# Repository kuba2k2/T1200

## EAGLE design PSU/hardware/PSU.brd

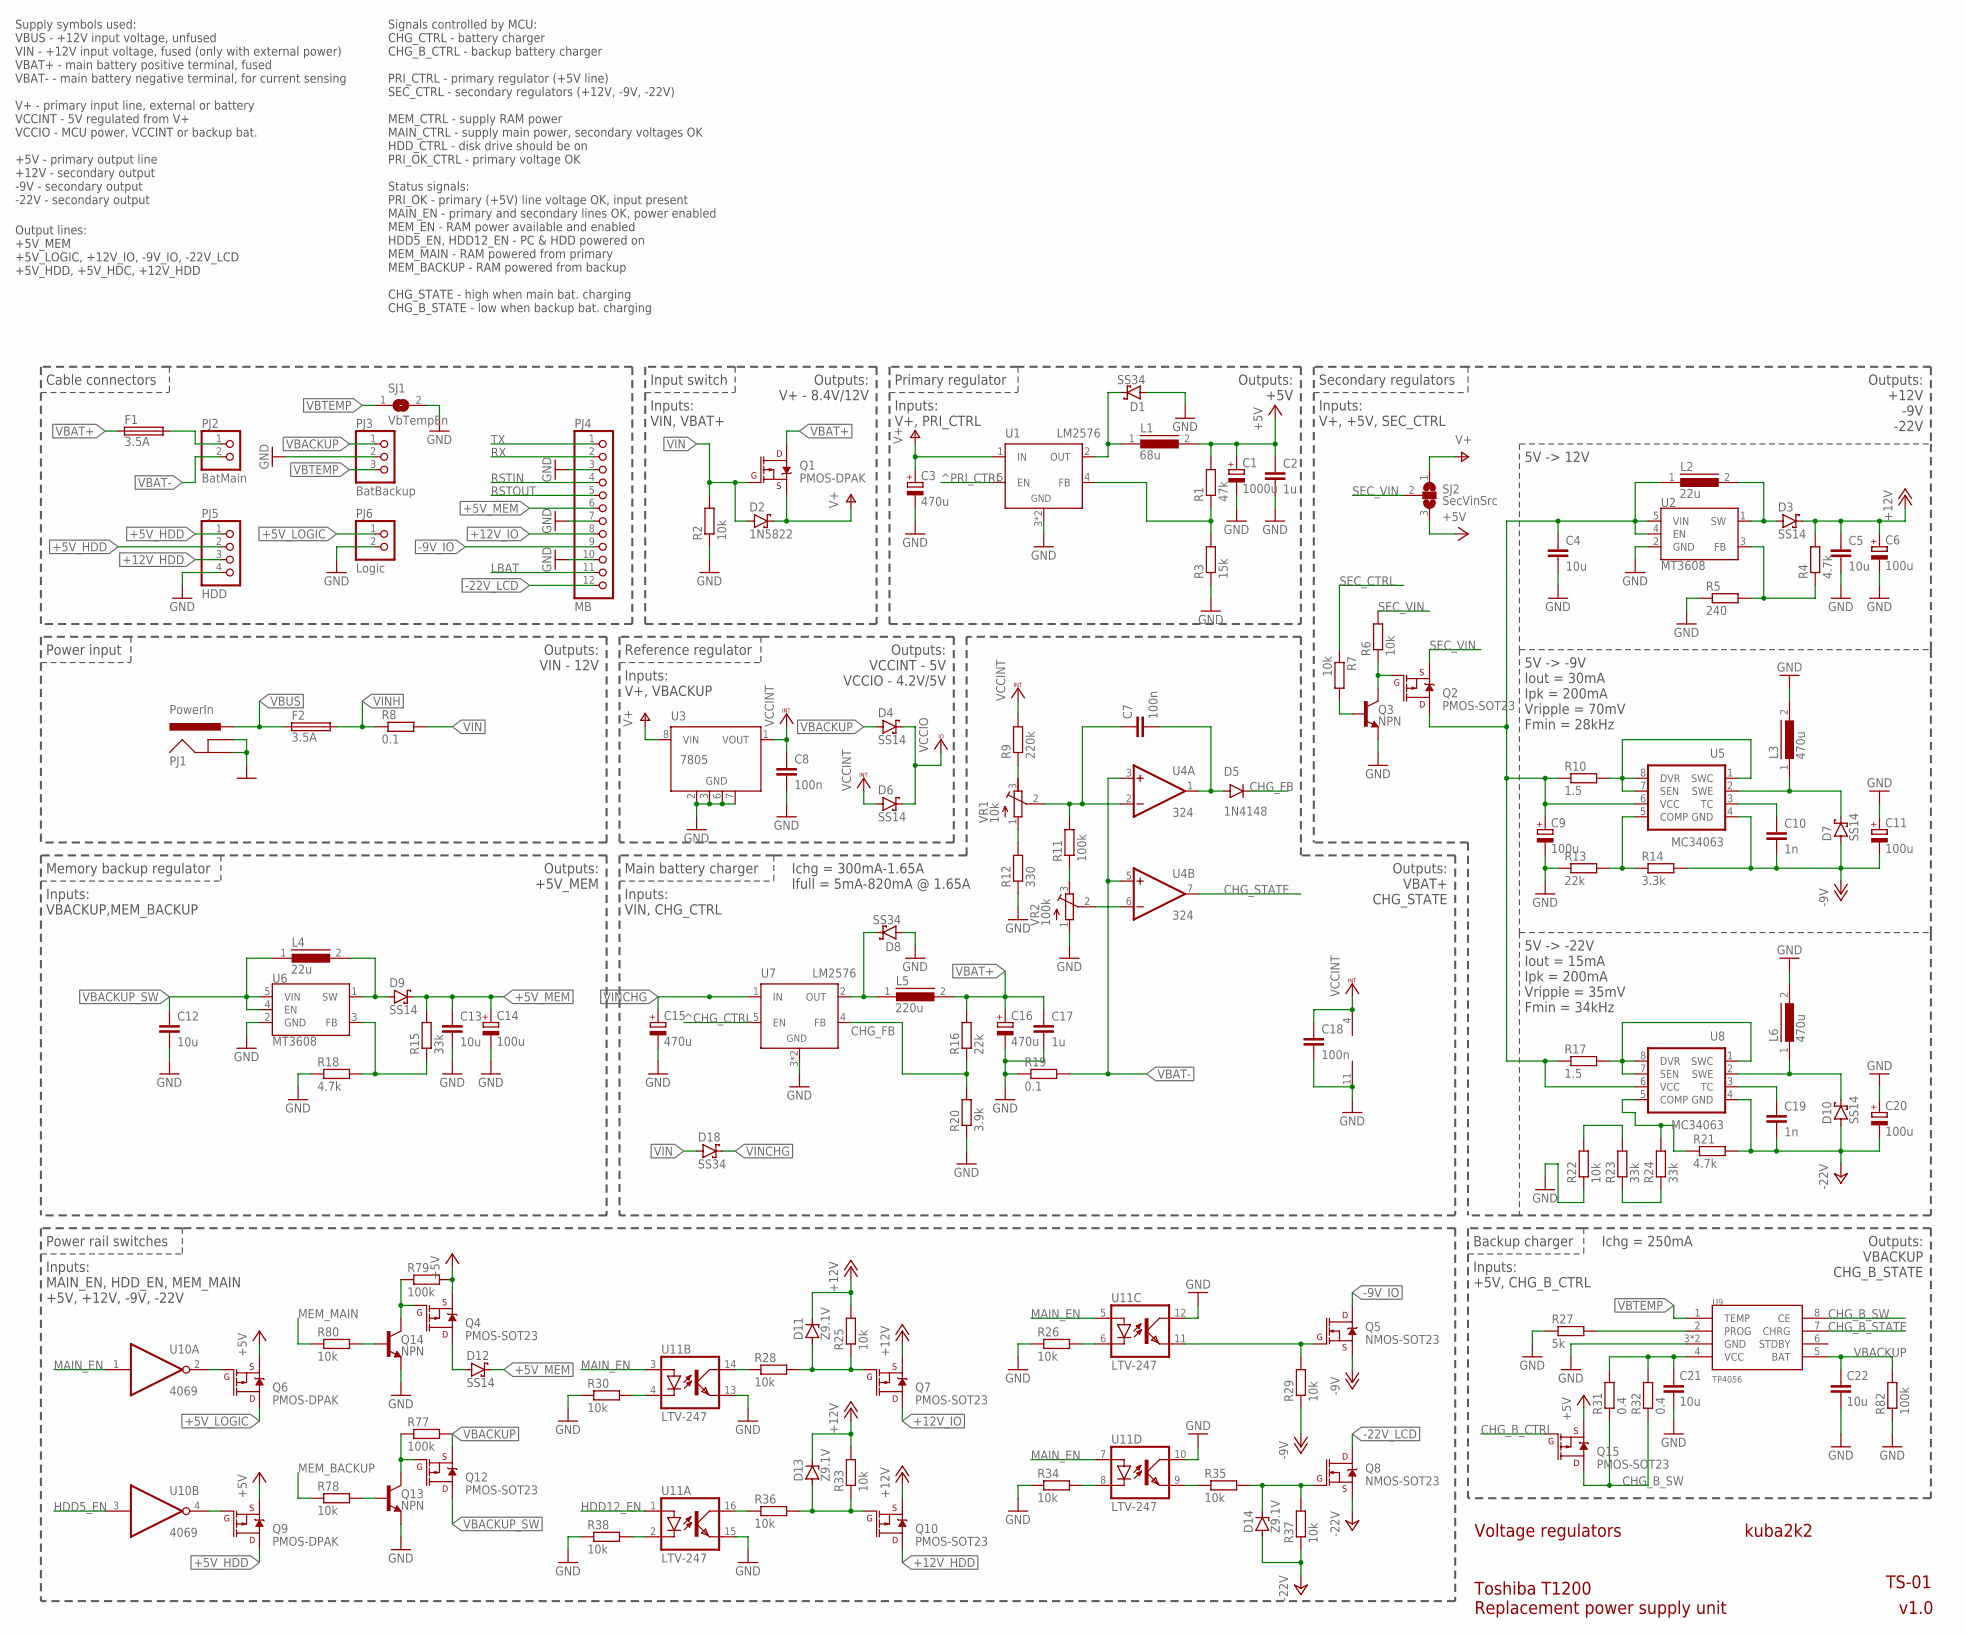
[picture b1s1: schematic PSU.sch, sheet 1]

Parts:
C1: 1000u; E5-10,5
C2, C17: 1u; C050-024X044
C3, C15, C16: 470u; E3,5-8
C4, C5, C12, C13, C21, C22: 10u; C1206
C6, C9, C11, C14, C20: 100u; E3,5-8
C7, C8, C18: 100n; C0805
C10, C19: 1n; C0805
D1, D8, D18: SS34; SMC
D2: 1N5822; F126Z12
D3, D4, D6, D7, D9, D10, D12: SS14; DO-214AC
D5: 1N4148; DO35-7
D11, D13, D14: Z9.1V; DO34Z7
F1, F2: 3.5A; 2512
L1: 68u; SFT1030
L2, L4: 22u; DR127
L3, L6: 470u; COIL0608
L5: 220u; SFT1030
PJ1: PowerIn; POWER_JACK_PTH
PJ2: BatMain; JST-PH2-4.00
PJ3: BatBackup; JST-PH3
PJ4: MB; JST-PH12
PJ5: HDD; JST-PH4-2.54
PJ6: Logic; JST-PH2-2.54
Q1, Q6, Q9: PMOS-DPAK; TO-252/DPAK
Q2, Q4, Q7, Q10, Q12, Q15: PMOS-SOT23; SOT23-3
Q3, Q13, Q14: NPN; SOT23-3
Q5, Q8: NMOS-SOT23; SOT23-3
R1: 47k; R0805
R2, R6, R7, R22, R25, R26, R28, R29, R30, R33, R34, R35, R36, R37, R38, R78, R80: 10k; R0805
R3: 15k; R0805
R4, R18, R21: 4.7k; R0805
R5: 240; R0805
R8, R19: 0.1; 0411/15
R9: 220k; R0805
R10, R17: 1.5; 0207/10
R11, R77, R79, R82: 100k; R0805
R12: 330; R0805
R13, R16: 22k; R0805
R14: 3.3k; R0805
R15, R23, R24: 33k; R0805
R20: 3.9k; R0805
R27: 5k; R0805
R31: 0.4; 0207/10
R32: 0.4; R1206
SJ1: VbTempEn; SJ
SJ2: SecVinSrc; SJ_2
U1, U7: LM2576; TO220-52-VIAHOLE
U2, U6: MT3608; SOT23-6
U3: 7805; SO08
U4: 324; SO14
U5, U8: MC34063; SO08
U9: TP4056; SO08-PAD
U10: 4069; SO14
U11: LTV-247; SO16-GULLWING
VR1: 10k; RTRIM3296W
VR2: 100k; RTRIM3296W

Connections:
+5V: C1.+, C2.1, L1.2, Q4.2 (S), Q6.3 (S), Q9.3 (S), Q15.2 (S), R1.2, R79.2, SJ2.3; also elsewhere on the board
+5VHDD_G: Q9.1 (G), U10.4 (O)
+5VLOG_G: Q6.1 (G), U10.2 (O)
+5VMEM_B: Q14.1 (B), R80.2
+5VMEM_D: D12.A, Q4.3 (D)
+5VMEM_G: Q4.1 (G), Q14.3 (C), R79.1
+5V_HDD: PJ5.1, PJ5.2, Q9.2 (D)
+5V_LOGIC: PJ6.1, Q6.2 (D)
+5V_MEM: C13.1, C14.+, D9.C, D12.C, PJ4.6, R15.2; also elsewhere on the board
+12V: C5.1, C6.+, D3.C, D11.C, D13.C, Q7.2 (S), Q10.2 (S), R4.2, R25.2, R33.2; also elsewhere on the board
+12VHDD_C: R36.1, U11.16 (COL)
+12VHDD_G: D13.A, Q10.1 (G), R33.1, R36.2
+12VHDD_N: R38.2, U11.2 (C)
+12VIO_C: R28.1, U11.14 (COL)
+12VIO_G: D11.A, Q7.1 (G), R25.1, R28.2
+12VIO_N: R30.2, U11.4 (C)
+12V_FB: R4.1, R5.2, U2.3 (FB)
+12V_HDD: PJ5.3, Q10.3 (D)
+12V_IO: PJ4.8, Q7.3 (D)
+12V_SW: D3.A, L2.2, U2.1 (SW)
-9V: C10.2, C11.-, D7.A, Q5.2 (S), R14.2, R29.1, U5.4 (GND); also elsewhere on the board
-9VIO_G: Q5.1 (G), R29.2, U11.11 (EMIT)
-9VIO_N: R26.2, U11.6 (C)
-9V_COMP: R13.2, R14.1, U5.5 (COMP)
-9V_IO: PJ4.9, Q5.3 (D)
-9V_SWC: R10.2, U5.1 (SWC), U5.7 (SEN), U5.8 (DVR)
-9V_SWE: D7.C, L3.1, U5.2 (SWE)
-9V_TC: C10.1, U5.3 (TC)
-22V: C19.2, C20.-, D10.A, D14.A, Q8.2 (S), R21.2, R37.1, U8.4 (GND); also elsewhere on the board
-22VLCD_E: R35.1, U11.9 (EMIT)
-22VLCD_G: D14.C, Q8.1 (G), R35.2, R37.2
-22VLCD_N: R34.2, U11.8 (C)
-22V_COMP1: R21.1, R24.2, U8.5 (COMP)
-22V_COMP2: R23.1, R24.1
-22V_COMP3: R22.2, R23.2
-22V_LCD: PJ4.12, Q8.3 (D)
-22V_SWC: R17.2, U8.1 (SWC), U8.7 (SEN), U8.8 (DVR)
-22V_SWE: D10.C, L6.1, U8.2 (SWE)
-22V_TC: C19.1, U8.3 (TC)
CC_VAL: C7.1, R11.2, U4.2 (-IN), VR1.2 (S)
CHG_B_CTRL: Q15.1 (G); also elsewhere on the board
CHG_B_PROG: R27.2, U9.2 (PROG)
CHG_B_STATE: U9.7 (CHRG); also elsewhere on the board
CHG_B_SW: Q15.3 (D), R31.1, R32.1, U9.8 (CE)
CHG_B_VCC: C21.1, R31.2, R32.2, U9.4 (VCC)
CHG_DIV1: R11.1, VR2.3 (E)
CHG_DIV2: R12.2, VR1.1 (A)
CHG_DIV3: R9.1, VR1.3 (E)
CHG_FB: D5.C, R16.1, R20.2, U7.4 (FB)
CHG_FB_OUT: C7.2, D5.A, U4.1 (OUT)
CHG_OUT: D8.C, L5.1, U7.2 (OUT)
CHG_STATE: U4.7 (OUT); also elsewhere on the board
FULL_VAL: U4.6 (-IN), VR2.2 (S)
GND: C1.-, C2.2, C3.-, C4.2, C5.2, C6.-, C8.2, C9.-, C11.+, C12.2, C13.2, C14.-, C15.-, C16.-, C17.2, C18.2, C20.+, C21.2, C22.2, D1.A, D8.A, L3.2, L6.2, PJ1.GND, PJ1.GNDBREAK, PJ3.2, PJ4.3, PJ4.7, PJ4.10, PJ5.4, PJ6.2, Q3.2 (E), Q13.2 (E), Q14.2 (E), R2.1, R3.1, R5.1, R12.1, R13.1, R18.1, R19.1, R20.1, R22.1, R26.1, R27.1, R30.1, R34.1, R38.1, R82.1, SJ1.2, U1.3 (GND), U1.TAB (GND), U2.2 (GND), U3.2 (GND), U3.3 (GND), U3.6 (GND), U3.7 (GND), U4.11 (V-), U6.2 (GND), U7.3 (GND), U7.TAB (GND), U9.3 (GND), U9.PAD (GND), U11.10 (COL), U11.12 (COL), U11.13 (EMIT), U11.15 (EMIT), VR2.1 (A); also elsewhere on the board
HDD5_EN: U10.3 (I); also elsewhere on the board
HDD12_EN: U11.1 (A); also elsewhere on the board
LBAT: PJ4.11; also elsewhere on the board
MAIN_EN: U10.1 (I), U11.3 (A), U11.5 (A), U11.7 (A); also elsewhere on the board
MB_FB: R15.1, R18.2, U6.3 (FB)
MB_SW: D9.A, L4.2, U6.1 (SW)
MEM_BACKUP: R78.1; also elsewhere on the board
MEM_MAIN: R80.1; also elsewhere on the board
PRI_FB: R1.1, R3.2, U1.4 (FB)
PRI_OUT: D1.C, L1.1, U1.2 (OUT)
RSTIN: PJ4.4; also elsewhere on the board
RSTOUT: PJ4.5; also elsewhere on the board
RX: PJ4.2; also elsewhere on the board
SECV_B: Q3.1 (B), R7.2
SECV_G: Q2.1 (G), Q3.3 (C), R6.1
SEC_CTRL: R7.1; also elsewhere on the board
SEC_VIN: Q2.2 (S), R6.2, SJ2.2
SEC_VIN_SW: C4.1, C9.+, L2.1, Q2.3 (D), R10.1, R17.1, U2.4 (EN), U2.5 (VIN), U5.6 (VCC), U8.6 (VCC)
TX: PJ4.1; also elsewhere on the board
V+: C3.+, D2.C, Q1.3 (S), SJ2.1, U1.1 (IN), U3.8 (VIN); also elsewhere on the board
VBACKUP: C22.1, D4.A, PJ3.1, Q12.2 (S), R77.2, R82.2, U9.5 (BAT); also elsewhere on the board
VBACKUP_SW: C12.1, L4.1, Q12.3 (D), U6.4 (EN), U6.5 (VIN)
VBACKUP_SW_B: Q13.1 (B), R78.2
VBACKUP_SW_G: Q12.1 (G), Q13.3 (C), R77.1
VBAT+: C16.+, C17.1, F1.1, L5.2, Q1.2 (D), R16.2; also elsewhere on the board
VBAT-: PJ2.2, R19.2, U4.3 (+IN), U4.5 (+IN); also elsewhere on the board
VBAT_RAW: F1.2, PJ2.1
VBTEMP: PJ3.3, SJ1.1, U9.1 (TEMP)
VBUS: F2.1, PJ1.PWR
VCCINT: C8.1, C18.1, D6.A, R9.2, U3.1 (VOUT), U4.4 (V+); also elsewhere on the board
VCCIO: D4.C, D6.C; also elsewhere on the board
VIN: D2.A, D18.A, Q1.1 (G), R2.2, R8.2; also elsewhere on the board
VINCHG: C15.+, D18.C, U7.1 (IN)
VINH: F2.2, R8.1; also elsewhere on the board
^CHG_CTRL: U7.5 (EN); also elsewhere on the board
^PRI_CTRL: U1.5 (EN); also elsewhere on the board

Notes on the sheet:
Supply symbols used: VBUS - +12V input voltage, unfused VIN - +12V input voltage, fused (only with external power) VBAT+ - main battery positive terminal, fused VBAT- - main battery negative terminal, for current sensing V+ - primary input line, external or battery VCCINT - 5V regulated from V+ VCC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
Signals controlled by MCU: CHG_CTRL - battery charger CHG_B_CTRL - backup battery charger PRI_CTRL - primary regulator (+5V line) SEC_CTRL - secondary regulators (+12V, -9V, -22V) MEM_CTRL - supply RAM power MAIN_CTRL - supply main power, secondary voltages OK HDD_CTRL - disk drive should be on PRI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
Output lines: +5V_MEM +5V_LOGIC, +12V_IO, -9V_IO, -22V_LCD +5V_HDD, +5V_HDC, +12V_HDD
Primary regulator
Cable connectors
Power input
Outputs: VIN - 12V
Input switch
Outputs: V+ - 8.4V/12V
Outputs: +5V
Inputs: V+, PRI_CTRL
Inputs: VIN, VBAT+
Secondary regulators
Inputs: V+, +5V, SEC_CTRL
Outputs: +12V -9V -22V
5V -> 12V
5V -> -9V Iout = 30mA Ipk = 200mA Vripple = 70mV Fmin = 28kHz
5V -> -22V Iout = 15mA Ipk = 200mA Vripple = 35mV Fmin = 34kHz
Backup charger
Ichg = 250mA
Inputs: +5V, CHG_B_CTRL
Outputs: VBACKUP CHG_B_STATE
Ichg = 300mA-1.65A Ifull = 5mA-820mA @ 1.65A
Memory backup regulator
Inputs: VBACKUP,MEM_BACKUP
Outputs: +5V_MEM
Reference regulator
Inputs: V+, VBACKUP
Outputs: VCCINT - 5V VCCIO - 4.2V/5V
Main battery charger
Inputs: VIN, CHG_CTRL
Outputs: VBAT+ CHG_STATE
Voltage regulators
Power rail switches
Inputs: MAIN_EN, HDD_EN, MEM_MAIN +5V, +12V, -9V, -22V
kuba2k2
TS-01
v1.0
Toshiba T1200 Replacement power supply unit

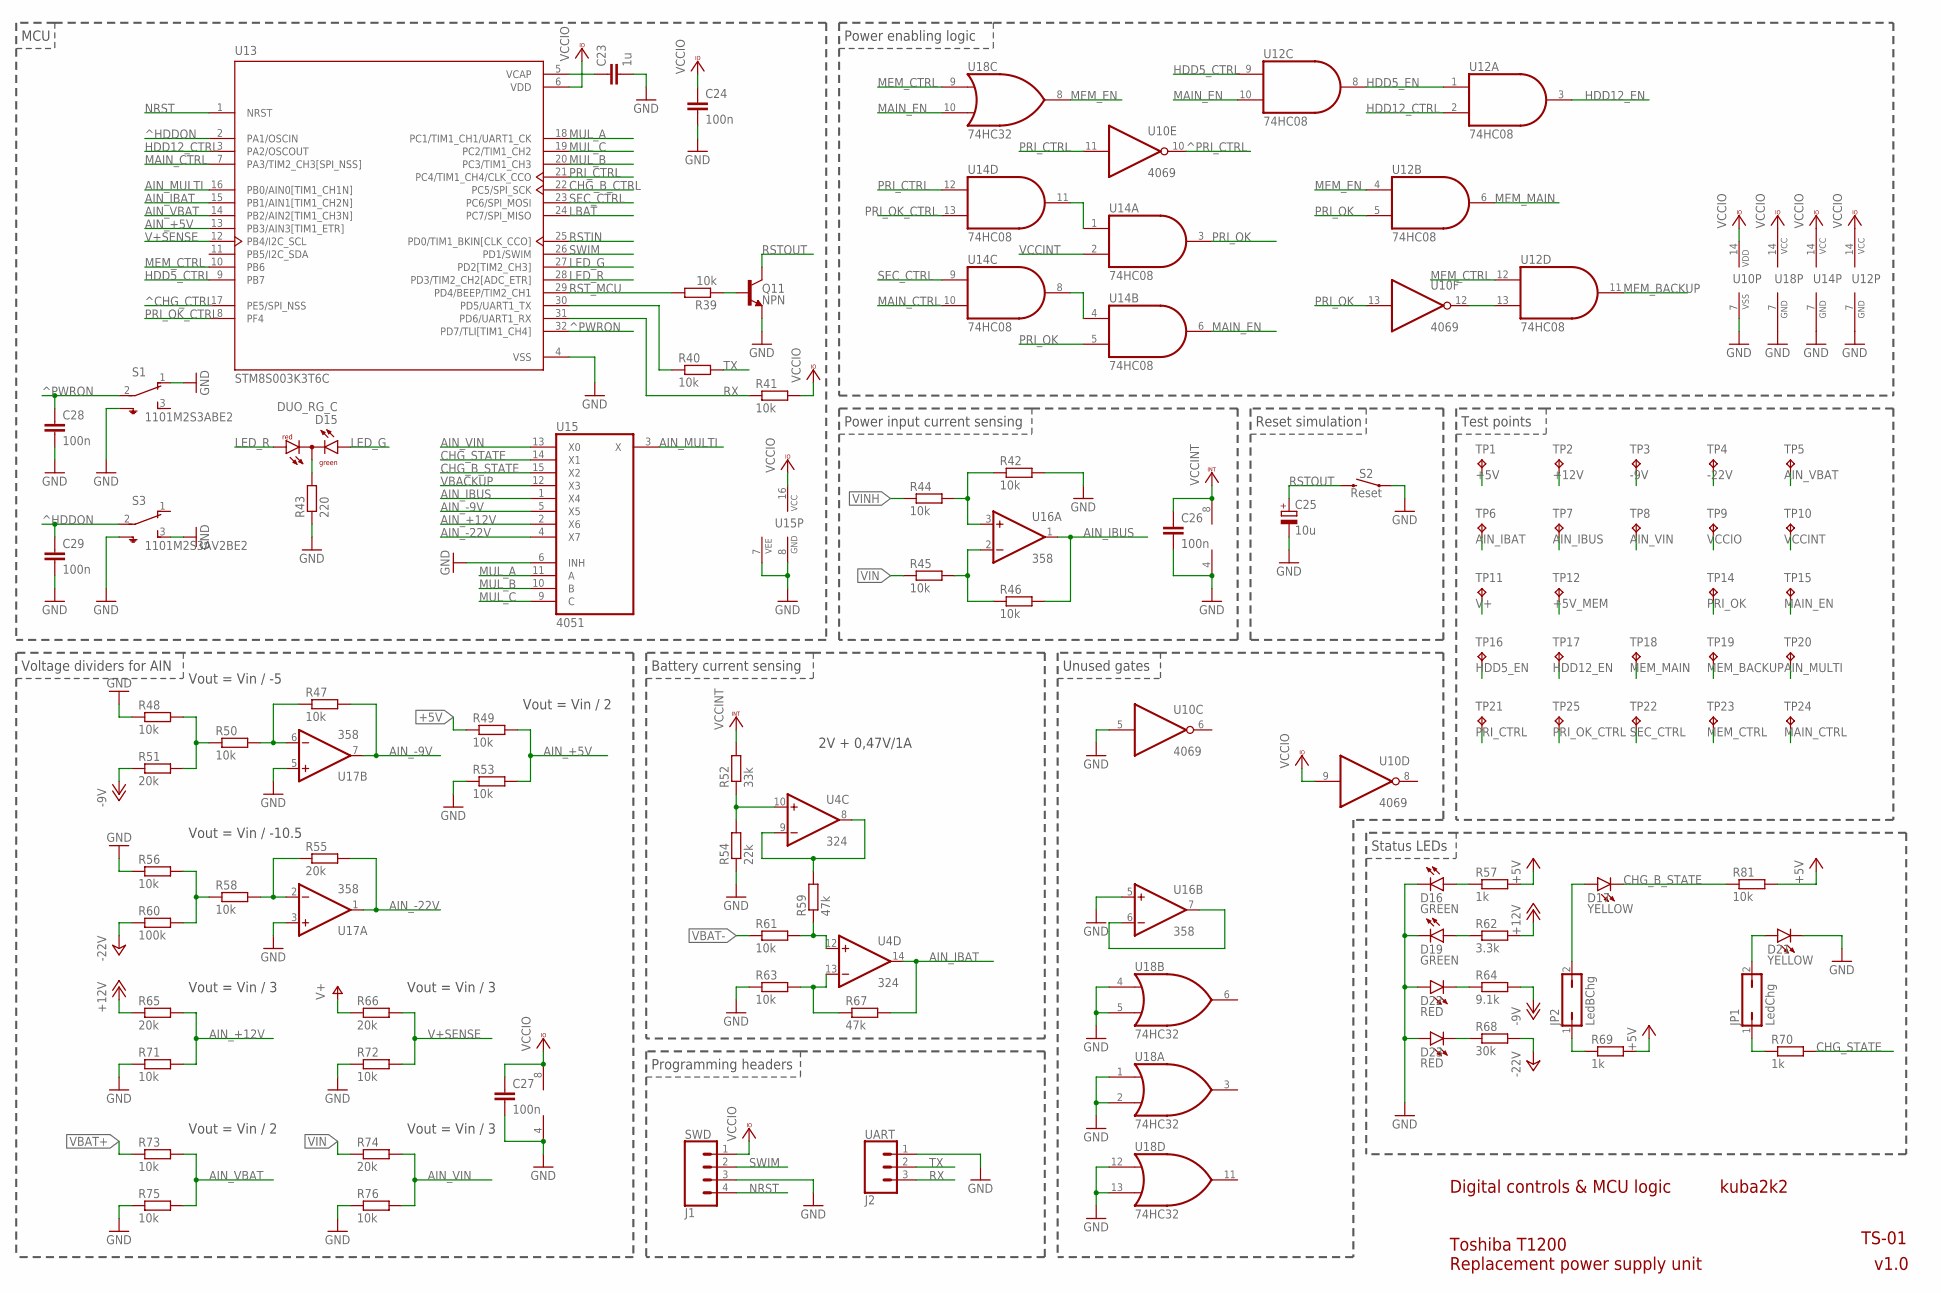
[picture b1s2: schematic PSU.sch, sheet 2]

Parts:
C23: 1u; C050-024X044
C24, C26, C27, C28, C29: 100n; C0805
C25: 10u; E2-5
D15: DUO_RG_C; DUOLED-C-5MM
D16, D19: GREEN; CHIP-LED0805
D17, D21: YELLOW; CHIP-LED0805
D22, D23: RED; CHIP-LED0805
J1: SWD; 1X04
J2: UART; 1X03
JP1: LedChg; JP1
JP2: LedBChg; JP1
Q11: NPN; SOT23-3
R39, R40, R41, R42, R44, R45, R46, R47, R48, R49, R50, R53, R56, R58, R61, R63, R71, R72, R73, R75, R76, R81: 10k; R0805
R43: 220; R0805
R51, R55, R65, R66, R74: 20k; R0805
R52: 33k; R0805
R54: 22k; R0805
R57, R69, R70: 1k; R0805
R59, R67: 47k; R0805
R60: 100k; R0805
R62: 3.3k; R0805
R64: 9.1k; R0805
R68: 30k; R0805
S1: 1101M2S3ABE2
S2: Reset; TACTILE_SWITCH_SMD_6.2MM_TALL
S3: 1101M2S3AV2BE2
TP1, TP2, TP3, TP4, TP5, TP6, TP7, TP8, TP9, TP10, TP11, TP12, TP14, TP15, TP16, TP17, TP18, TP19, TP20, TP21, TP22, TP23, TP24, TP25: TPB1,27; B1,27
U4: 324; SO14
U10: 4069; SO14
U12, U14: 74HC08; SO14
U13: STM8S003K3T6C; QFP80P900X900X160-32N
U15: 4051; SO16
U16, U17: 358; SO08
U18: 74HC32; SO14

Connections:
+5V: R49.1, R57.2, R69.2, R81.2, TP1.TP; also elsewhere on the board
+5V_MEM: TP12.TP; also elsewhere on the board
+12V: R62.2, R65.1, TP2.TP; also elsewhere on the board
-9V: R51.1, R64.2, TP3.TP; also elsewhere on the board
-22V: R60.1, R68.2, TP4.TP; also elsewhere on the board
AIN9DIV: R48.2, R50.1, R51.2
AIN9N: R47.1, R50.2, U17.6 (-IN)
AIN22DIV: R56.2, R58.1, R60.2
AIN22N: R55.1, R58.2, U17.2 (-IN)
AIN_+5V: R49.2, R53.2, U13.13 (PB3/AIN3[TIM1_ETR])
AIN_+12V: R65.2, R71.2, U15.2 (X6)
AIN_-9V: R47.2, U15.5 (X5), U17.7 (OUT)
AIN_-22V: R55.2, U15.4 (X7), U17.1 (OUT)
AIN_IBAT: R67.2, TP6.TP, U4.14 (OUT), U13.15 (PB1/AIN1[TIM1_CH2N])
AIN_IBUS: R46.2, TP7.TP, U15.1 (X4), U16.1 (OUT)
AIN_MULTI: TP20.TP, U13.16 (PB0/AIN0[TIM1_CH1N]), U15.3 (X)
AIN_VBAT: R73.2, R75.2, TP5.TP, U13.14 (PB2/AIN2[TIM1_CH3N])
AIN_VIN: R74.2, R76.2, TP8.TP, U15.13 (X0)
CHG_B_CTRL: U13.22 (PC5/SPI_SCK); also elsewhere on the board
CHG_B_STATE: D17.C, R81.1, U15.15 (X2); also elsewhere on the board
CHG_STATE: R70.2, U15.14 (X1); also elsewhere on the board
GND: C23.2, C24.2, C25.-, C26.2, C27.2, C28.2, C29.2, D16.C, D19.C, D21.C, D22.A, D23.A, J1.3, J2.1, Q11.2 (E), R42.2, R43.1, R48.1, R53.1, R54.1, R56.1, R63.1, R71.1, R72.1, R75.1, R76.1, S1.1 (O), S1.S1 (SH), S1.S2 (SH), S2.A2 (1), S3.3 (S), S3.S1 (SH), S3.S2 (SH), U10.5 (I), U10.7 (VSS), U12.7 (GND), U13.4 (VSS), U14.7 (GND), U15.6 (INH), U15.7 (VEE), U15.8 (GND), U16.4 (V-), U16.5 (+IN), U17.3 (+IN), U17.4 (V-), U17.5 (+IN), U18.1 (I0), U18.2 (I1), U18.4 (I0), U18.5 (I1), U18.7 (GND), U18.12 (I0), U18.13 (I1); also elsewhere on the board
HDD5_CTRL: U12.9 (I0), U13.9 (PB7)
HDD5_EN: TP16.TP, U12.1 (I0), U12.8 (O); also elsewhere on the board
HDD12_CTRL: U12.2 (I1), U13.3 (PA2/OSCOUT)
HDD12_EN: TP17.TP, U12.3 (O); also elsewhere on the board
IBAT_DIVN: R59.2, U4.8 (OUT), U4.9 (-IN)
IBAT_DIVP: R52.1, R54.2, U4.10 (+IN)
IBAT_N: R63.2, R67.1, U4.13 (-IN)
IBAT_P: R59.1, R61.2, U4.12 (+IN)
IBUS_N: R45.2, R46.1, U16.2 (-IN)
IBUS_P: R42.1, R44.2, U16.3 (+IN)
LBAT: U13.24 (PC7/SPI_MISO); also elsewhere on the board
LED1_+5: D16.A, R57.1
LED1_+12: D19.A, R62.1
LED1_-9: D22.C, R64.1
LED1_-22: D23.C, R68.1
LED2_EN: D17.A, JP2.2
LED2_P: JP2.1, R69.1
LED3_EN: D21.A, JP1.2
LED3_P: JP1.1, R70.1
LED_CC: D15.C, R43.2
LED_G: D15.AX (AG), U13.27 (PD2[TIM2_CH3])
LED_R: D15.AR, U13.28 (PD3/TIM2_CH2[ADC_ETR])
MAIN_CTRL: TP24.TP, U13.7 (PA3/TIM2_CH3[SPI_NSS]), U14.10 (I1)
MAIN_EN: TP15.TP, U12.10 (I1), U14.6 (O), U18.10 (I1); also elsewhere on the board
MAIN_MID: U14.4 (I0), U14.8 (O)
MB_MID: U10.12 (O), U12.13 (I1)
MEM_BACKUP: TP19.TP, U12.11 (O); also elsewhere on the board
MEM_CTRL: TP23.TP, U12.12 (I0), U13.10 (PB6), U18.9 (I0)
MEM_EN: U12.4 (I0), U18.8 (O)
MEM_MAIN: TP18.TP, U12.6 (O); also elsewhere on the board
MUL_A: U13.18 (PC1/TIM1_CH1/UART1_CK), U15.11 (A)
MUL_B: U13.20 (PC3/TIM1_CH3), U15.10 (B)
MUL_C: U13.19 (PC2/TIM1_CH2), U15.9 (C)
NRST: J1.4, U13.1 (NRST)
PRI_CTRL: TP21.TP, U10.11 (I), U13.21 (PC4/TIM1_CH4/CLK_CCO), U14.12 (I0)
PRI_MID: U14.1 (I0), U14.11 (O)
PRI_OK: TP14.TP, U10.13 (I), U12.5 (I1), U14.3 (O), U14.5 (I1)
PRI_OK_CTRL: TP25.TP, U13.8 (PF4), U14.13 (I1)
RSTIN: U13.25 (PD0/TIM1_BKIN[CLK_CCO]); also elsewhere on the board
RSTOUT: C25.+, Q11.3 (C), S2.B2 (2); also elsewhere on the board
RST_B: Q11.1 (B), R39.1
RST_MCU: R39.2, U13.29 (PD4/BEEP/TIM2_CH1)
RX: J2.3, R41.1, U13.31 (PD6/UART1_RX); also elsewhere on the board
SEC_CTRL: TP22.TP, U13.23 (PC6/SPI_MOSI), U14.9 (I0); also elsewhere on the board
SWIM: J1.2, U13.26 (PD1/SWIM)
TX: J2.2, R40.2; also elsewhere on the board
TX_MCU: R40.1, U13.30 (PD5/UART1_TX)
U18B: U16.6 (-IN), U16.7 (OUT)
V+: R66.1, TP11.TP; also elsewhere on the board
V+SENSE: R66.2, R72.2, U13.12 (PB4/I2C_SCL)
VBACKUP: U15.12 (X3); also elsewhere on the board
VBAT+: R73.1; also elsewhere on the board
VBAT-: R61.1; also elsewhere on the board
VCAP: C23.1, U13.5 (VCAP)
VCCINT: C26.1, R52.2, TP10.TP, U14.2 (I1), U16.8 (V+); also elsewhere on the board
VCCIO: C24.1, C27.1, J1.1, R41.2, TP9.TP, U10.9 (I), U10.14 (VDD), U12.14 (VCC), U13.6 (VDD), U14.14 (VCC), U15.16 (VCC), U17.8 (V+), U18.14 (VCC); also elsewhere on the board
VIN: R45.1, R74.1; also elsewhere on the board
VINH: R44.1; also elsewhere on the board
^CHG_CTRL: U13.17 (PE5/SPI_NSS); also elsewhere on the board
^HDDON: C29.1, S3.2, U13.2 (PA1/OSCIN)
^PRI_CTRL: U10.10 (O); also elsewhere on the board
^PWRON: C28.1, S1.2, U13.32 (PD7/TLI[TIM1_CH4])

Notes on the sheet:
MCU
Power enabling logic
Voltage dividers for AIN
Vout = Vin / -5
Vout = Vin / -10.5
Vout = Vin / 3
Vout = Vin / 2
Programming headers
Battery current sensing
2V + 0,47V/1A
Status LEDs
Power input current sensing
Unused gates
Reset simulation
Test points
Digital controls & MCU logic
kuba2k2
TS-01
v1.0
Toshiba T1200 Replacement power supply unit

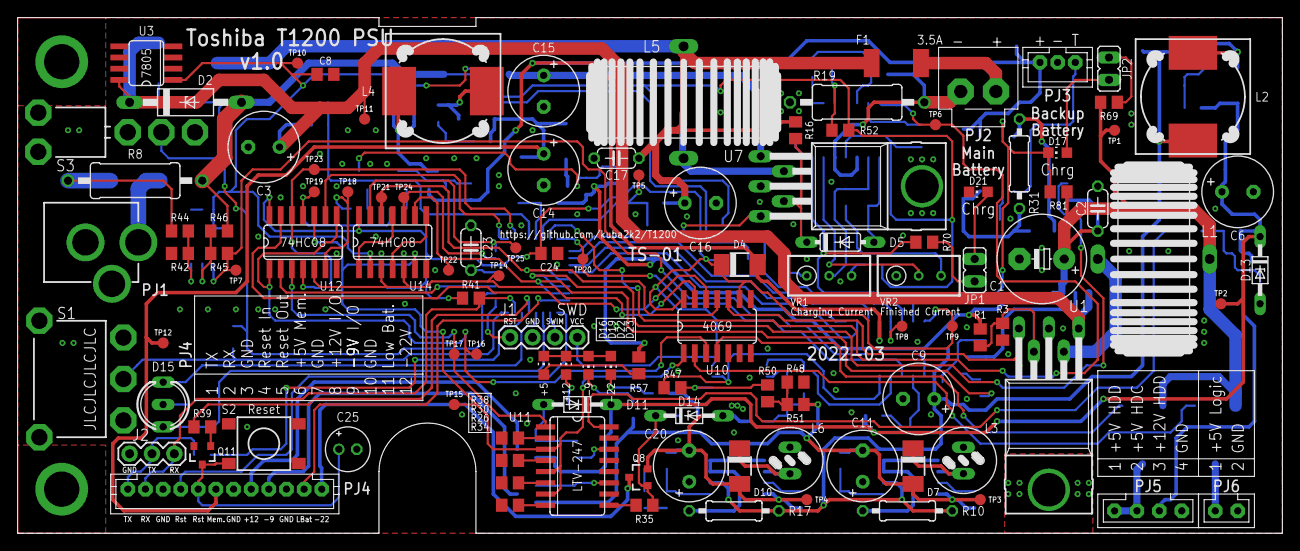
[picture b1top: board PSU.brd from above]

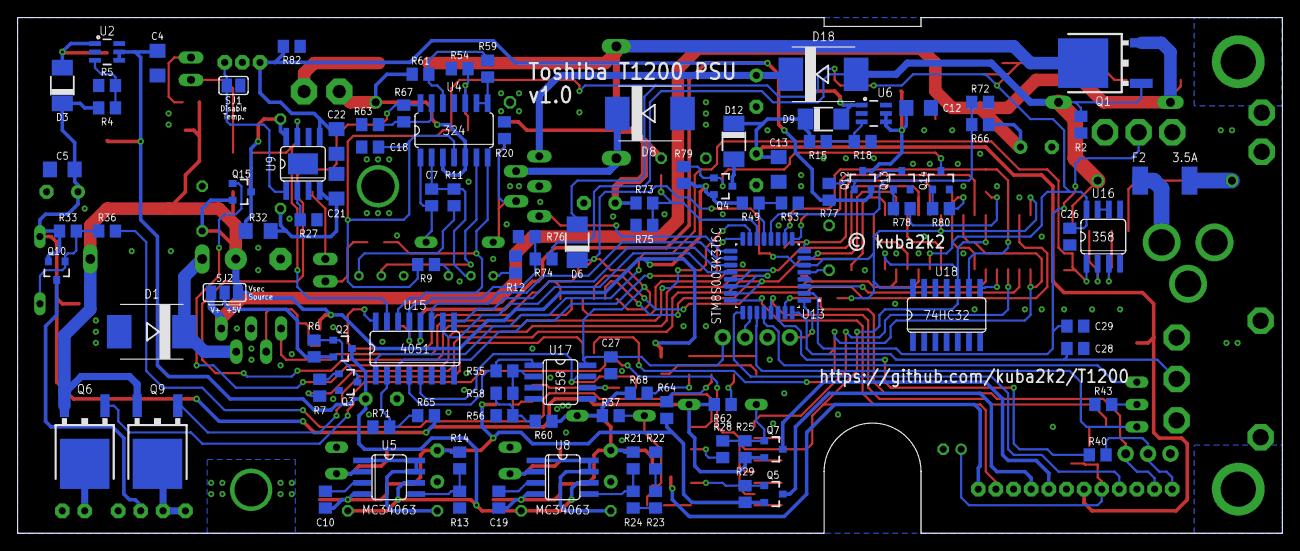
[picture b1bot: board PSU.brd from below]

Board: 2 copper layers, 143.5 x 58.5 mm, 215 parts (102 on the bottom side), 144 nets.

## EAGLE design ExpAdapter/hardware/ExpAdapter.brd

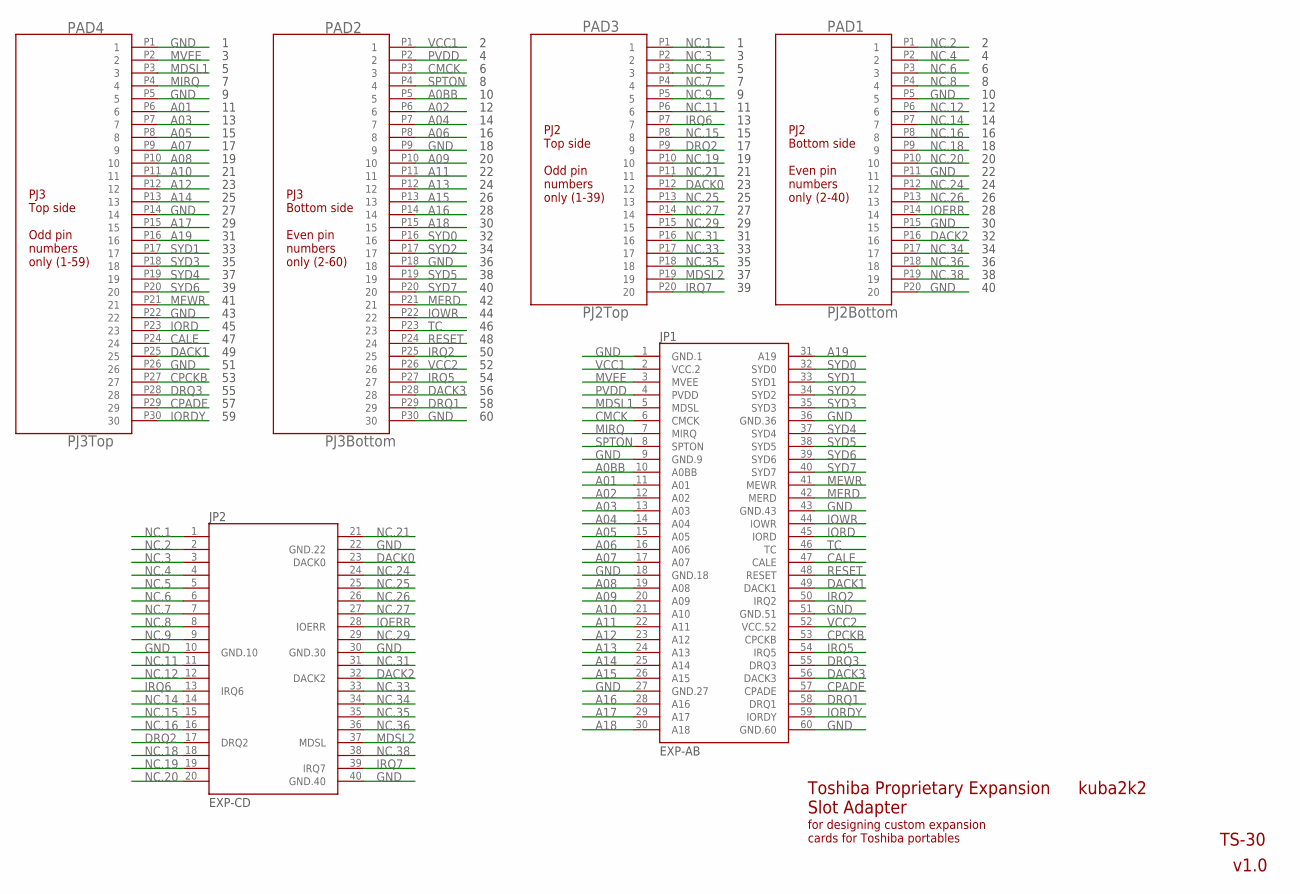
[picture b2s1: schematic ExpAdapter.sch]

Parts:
JP1: EXP-AB; CONN60
JP2: EXP-CD; CONN40
PAD1: PJ2Bottom; PAD20
PAD2: PJ3Bottom; PAD30
PAD3: PJ2Top; PAD20
PAD4: PJ3Top; PAD30

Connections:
A0BB: JP1.10 (A0BB), PAD2.P5 (5)
A01: JP1.11 (A01), PAD4.P6 (6)
A02: JP1.12 (A02), PAD2.P6 (6)
A03: JP1.13 (A03), PAD4.P7 (7)
A04: JP1.14 (A04), PAD2.P7 (7)
A05: JP1.15 (A05), PAD4.P8 (8)
A06: JP1.16 (A06), PAD2.P8 (8)
A07: JP1.17 (A07), PAD4.P9 (9)
A08: JP1.19 (A08), PAD4.P10 (10)
A09: JP1.20 (A09), PAD2.P10 (10)
A10: JP1.21 (A10), PAD4.P11 (11)
A11: JP1.22 (A11), PAD2.P11 (11)
A12: JP1.23 (A12), PAD4.P12 (12)
A13: JP1.24 (A13), PAD2.P12 (12)
A14: JP1.25 (A14), PAD4.P13 (13)
A15: JP1.26 (A15), PAD2.P13 (13)
A16: JP1.28 (A16), PAD2.P14 (14)
A17: JP1.29 (A17), PAD4.P15 (15)
A18: JP1.30 (A18), PAD2.P15 (15)
A19: JP1.31 (A19), PAD4.P16 (16)
CALE: JP1.47 (CALE), PAD4.P24 (24)
CMCK: JP1.6 (CMCK), PAD2.P3 (3)
CPADE: JP1.57 (CPADE), PAD4.P29 (29)
CPCKB: JP1.53 (CPCKB), PAD4.P27 (27)
DACK0: JP2.23 (DACK0), PAD3.P12 (12)
DACK1: JP1.49 (DACK1), PAD4.P25 (25)
DACK2: JP2.32 (DACK2), PAD1.P16 (16)
DACK3: JP1.56 (DACK3), PAD2.P28 (28)
DRQ1: JP1.58 (DRQ1), PAD2.P29 (29)
DRQ2: JP2.17 (DRQ2), PAD3.P9 (9)
DRQ3: JP1.55 (DRQ3), PAD4.P28 (28)
GND: JP1.1 (GND.1), JP1.9 (GND.9), JP1.18 (GND.18), JP1.27 (GND.27), JP1.36 (GND.36), JP1.43 (GND.43), JP1.51 (GND.51), JP1.60 (GND.60), JP2.10 (GND.10), JP2.22 (GND.22), JP2.30 (GND.30), JP2.40 (GND.40), PAD1.P5 (5), PAD1.P11 (11), PAD1.P15 (15), PAD1.P20 (20), PAD2.P9 (9), PAD2.P18 (18), PAD2.P30 (30), PAD4.P1 (1), PAD4.P5 (5), PAD4.P14 (14), PAD4.P22 (22), PAD4.P26 (26)
IOERR: JP2.28 (IOERR), PAD1.P14 (14)
IORD: JP1.45 (IORD), PAD4.P23 (23)
IORDY: JP1.59 (IORDY), PAD4.P30 (30)
IOWR: JP1.44 (IOWR), PAD2.P22 (22)
IRQ2: JP1.50 (IRQ2), PAD2.P25 (25)
IRQ5: JP1.54 (IRQ5), PAD2.P27 (27)
IRQ6: JP2.13 (IRQ6), PAD3.P7 (7)
IRQ7: JP2.39 (IRQ7), PAD3.P20 (20)
MDSL1: JP1.5 (MDSL), PAD4.P3 (3)
MDSL2: JP2.37 (MDSL), PAD3.P19 (19)
MERD: JP1.42 (MERD), PAD2.P21 (21)
MEWR: JP1.41 (MEWR), PAD4.P21 (21)
MIRQ: JP1.7 (MIRQ), PAD4.P4 (4)
MVEE: JP1.3 (MVEE), PAD4.P2 (2)
NC.1: JP2.1 (NC.1), PAD3.P1 (1)
NC.2: JP2.2 (NC.2), PAD1.P1 (1)
NC.3: JP2.3 (NC.3), PAD3.P2 (2)
NC.4: JP2.4 (NC.4), PAD1.P2 (2)
NC.5: JP2.5 (NC.5), PAD3.P3 (3)
NC.6: JP2.6 (NC.6), PAD1.P3 (3)
NC.7: JP2.7 (NC.7), PAD3.P4 (4)
NC.8: JP2.8 (NC.8), PAD1.P4 (4)
NC.9: JP2.9 (NC.9), PAD3.P5 (5)
NC.11: JP2.11 (NC.11), PAD3.P6 (6)
NC.12: JP2.12 (NC.12), PAD1.P6 (6)
NC.14: JP2.14 (NC.14), PAD1.P7 (7)
NC.15: JP2.15 (NC.15), PAD3.P8 (8)
NC.16: JP2.16 (NC.16), PAD1.P8 (8)
NC.18: JP2.18 (NC.18), PAD1.P9 (9)
NC.19: JP2.19 (NC.19), PAD3.P10 (10)
NC.20: JP2.20 (NC.20), PAD1.P10 (10)
NC.21: JP2.21 (NC.21), PAD3.P11 (11)
NC.24: JP2.24 (NC.24), PAD1.P12 (12)
NC.25: JP2.25 (NC.25), PAD3.P13 (13)
NC.26: JP2.26 (NC.26), PAD1.P13 (13)
NC.27: JP2.27 (NC.27), PAD3.P14 (14)
NC.29: JP2.29 (NC.29), PAD3.P15 (15)
NC.31: JP2.31 (NC.31), PAD3.P16 (16)
NC.33: JP2.33 (NC.33), PAD3.P17 (17)
NC.34: JP2.34 (NC.34), PAD1.P17 (17)
NC.35: JP2.35 (NC.35), PAD3.P18 (18)
NC.36: JP2.36 (NC.36), PAD1.P18 (18)
NC.38: JP2.38 (NC.38), PAD1.P19 (19)
PVDD: JP1.4 (PVDD), PAD2.P2 (2)
RESET: JP1.48 (RESET), PAD2.P24 (24)
SPTON: JP1.8 (SPTON), PAD2.P4 (4)
SYD0: JP1.32 (SYD0), PAD2.P16 (16)
SYD1: JP1.33 (SYD1), PAD4.P17 (17)
SYD2: JP1.34 (SYD2), PAD2.P17 (17)
SYD3: JP1.35 (SYD3), PAD4.P18 (18)
SYD4: JP1.37 (SYD4), PAD4.P19 (19)
SYD5: JP1.38 (SYD5), PAD2.P19 (19)
SYD6: JP1.39 (SYD6), PAD4.P20 (20)
SYD7: JP1.40 (SYD7), PAD2.P20 (20)
TC: JP1.46 (TC), PAD2.P23 (23)
VCC1: JP1.2 (VCC.2), PAD2.P1 (1)
VCC2: JP1.52 (VCC.52), PAD2.P26 (26)

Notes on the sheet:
PJ3 Top side Odd pin numbers only (1-59)
PJ3 Bottom side Even pin numbers only (2-60)
PJ2 Top side Odd pin numbers only (1-39)
PJ2 Bottom side Even pin numbers only (2-40)
kuba2k2
v1.0
TS-30
Toshiba Proprietary Expansion Slot Adapter
for designing custom expansion cards for Toshiba portables

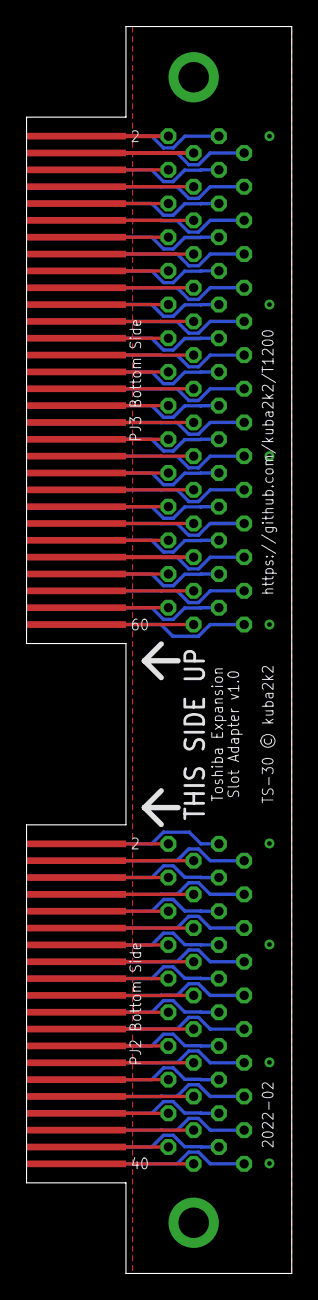
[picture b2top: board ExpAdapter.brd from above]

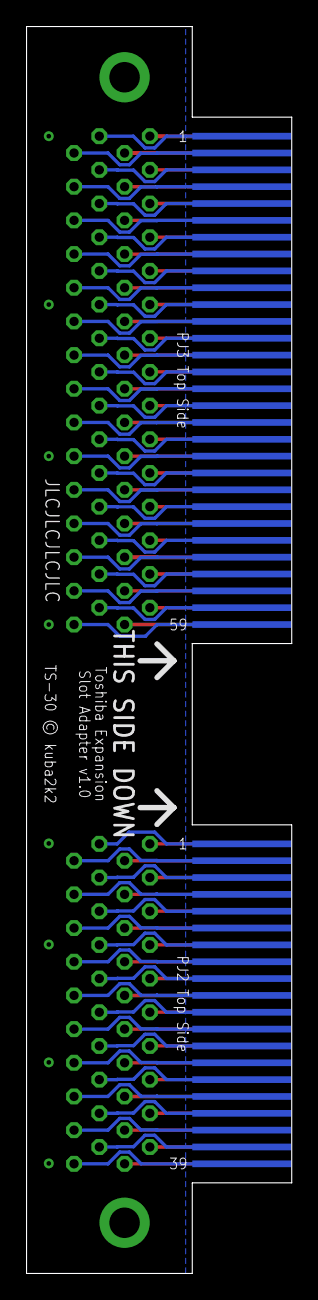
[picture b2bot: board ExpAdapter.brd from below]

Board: 2 copper layers, 20.0 x 94.0 mm, 6 parts (2 on the bottom side), 89 nets.

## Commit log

2022-03-07 [HW/ExpAdapter] Add design files
2022-03-07 [HW/ExpAdapter] Release v1.0
2022-03-07 Add hardware design license
2022-03-11 [HW/PSU] Add design files
2022-03-11 [HW/PSU] Release v1.0
2022-11-14 [HW/PSU] Fix MT3608 feedback divider values
2022-11-15 [HW/PSU] Fix secondary 12V regulator enabling
2022-12-03 [HW/PSU] Fix LM2576 enable signals level
2022-12-03 [HW/PSU] Fix backup regulator enabling
2023-04-05 [HW/PSU] Fix backup regulator enabling logic level
2023-04-05 [HW/PSU] Fix +5V_MEM enabling logic level
2023-04-09 [HW/PSU] Fix open-drain GPIO usage
2023-04-09 [HW/PSU] Fix backup charger enabling, remove standby LEDs
2023-04-09 [HW/PSU] Add switch debouncing
2023-04-11 [HW/PSU] Correct resistor values
2023-04-14 [HW/PSU] Fix Vbat to Vin voltage leak

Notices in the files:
ExpAdapter/hardware/ExpAdapter.brd:
TS-30 © kuba2k2
PSU/hardware/PSU.brd:
© kuba2k2
parts and their libraries:
SparkFun-Connectors: Licensing: Creative Commons ShareAlike 4.0 International - https://creativecommons.org/licenses/by-sa/4.0
